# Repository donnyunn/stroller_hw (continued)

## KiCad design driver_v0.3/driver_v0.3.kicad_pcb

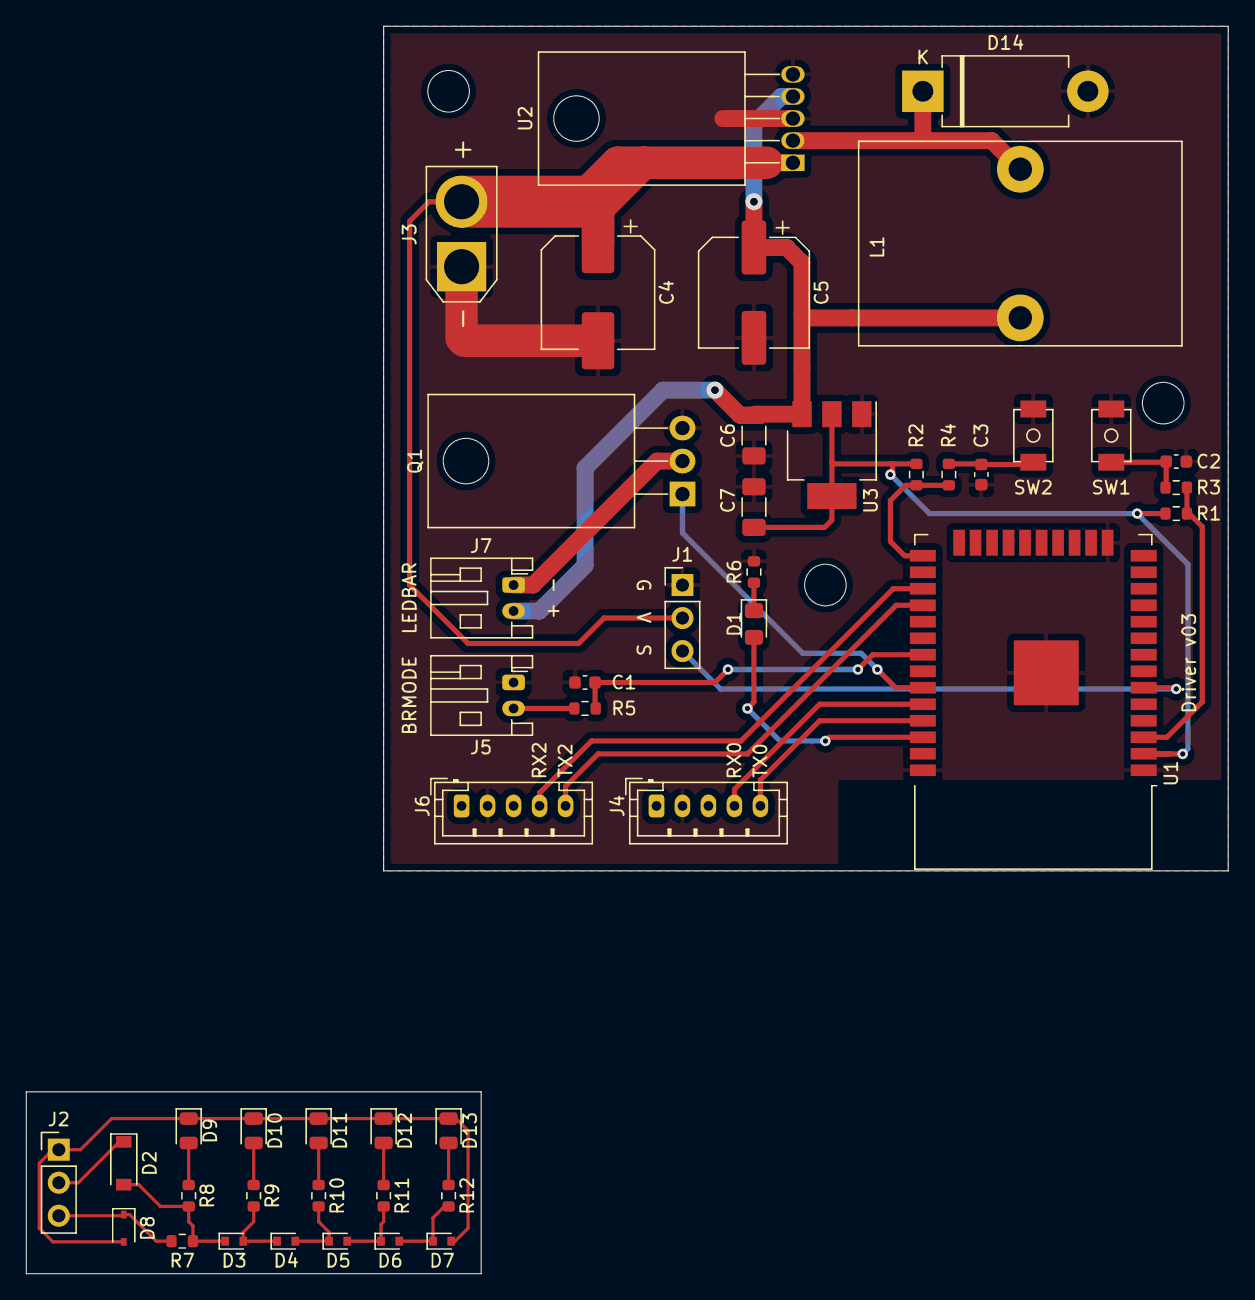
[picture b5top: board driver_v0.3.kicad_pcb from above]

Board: 2 copper layers, 92.5 x 96.0 mm, 47 parts (0 on the bottom side), 33 nets.

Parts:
C1, C2, C3: 0.1u; C_0603_1608Metric
C4: 100uF/50V; CP_Elec_8x10.5
C5: 1000uF/6.3V; CP_Elec_8x11.9
C6, C7: 4.7uF/3216; C_1206_3216Metric_Pad1.33x1.80mm_HandSolder
D1: LED; LED_0805_2012Metric_Pad1.15x1.40mm_HandSolder
D2: zenor/32v; D_SOD-123
D3, D4, D5, D6, D7: zenor/2v; D_SOD-523
D8: zenor/3.3v; D_SOD-323
D9, D10, D11, D12, D13: RED; LED_0805_2012Metric
D14: 1N5822; D_DO-201AD_P12.70mm_Horizontal
J1, J2: Conn_01x03; PinHeader_1x03_P2.54mm_Vertical
J3: Batt; AMASS_XT30U-F_1x02_P5.0mm_Vertical
J4: UART0; JST_PH_B5B-PH-K_1x05_P2.00mm_Vertical
J5: Button; JST_PH_S2B-PH-K_1x02_P2.00mm_Horizontal
J6: UART2; JST_PH_B5B-PH-K_1x05_P2.00mm_Vertical
J7: LED; JST_PH_S2B-PH-K_1x02_P2.00mm_Horizontal
L1: 100uH; L_Toroid_Vertical_L24.6mm_W15.5mm_P11.44mm_Pulse_KM-4
Q1: N-FET; TO-220-3_Horizontal_TabDown
R1, R2, R7: 100k; R_0603_1608Metric
R3, R4, R5, R12: 100; R_0603_1608Metric
R6, R8: 560; R_0603_1608Metric
R9: 430; R_0603_1608Metric
R10: 280; R_0603_1608Metric
R11: 150; R_0603_1608Metric
SW1, SW2: EN; CTT-1135P1
U1: ESP32-WROOM-32
U2: LM2576HVT-5; TO-220-5_Horizontal_TabDown
U3: LD1117S33TR_SOT223; SOT-223-3_TabPin2

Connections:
/Battery Level Guage/BATT_10CELL: D2.1, J2.2
/Battery Level Guage/BATT_GND: D7.2, D8.2, D9.1, D10.1, D11.1, D12.1, D13.1, J2.1
/Battery Level Guage/BATT_SENS: D8.1, J2.3, R7.1
BOOT: R2.2, R4.1, U1.25
EN: R1.2, R3.1, U1.3
Earth: C1.2, C2.2, C3.2, C4.2, C5.2, C6.2, C7.2, D14.2, J1.1, J3.1, J4.2, J5.1, J6.2, Q1.3, R6.2, SW1.1, SW2.1, U1.1, U1.15, U1.38, U1.39, U2.3, U2.5, U3.1
IO19(BRMODE): C1.1, R5.1, U1.31
IO21(LED): Q1.1, U1.33
IO22(IND): D1.2, U1.36
IO34(LVSENS): J1.3, U1.6
unnamed: C2.1, R3.2, SW1.2
unnamed: C3.1, R4.2, SW2.2
unnamed: D1.1, R6.1
unnamed: D2.2, D3.1, R7.2, R8.2
unnamed: D3.2, D4.1, R9.2
unnamed: D4.2, D5.1, R10.2
unnamed: D5.2, D6.1, R11.2
unnamed: D6.2, D7.1, R12.2
unnamed: D9.2, R8.1
unnamed: D10.2, R9.1
unnamed: D11.2, R10.1
unnamed: D12.2, R11.1
unnamed: D13.2, R12.1
unnamed: D14.1, L1.1, U2.2
unnamed: J5.2, R5.2
unnamed: J7.1, Q1.2
RXD0: J4.4, U1.34
RXD2: J6.4, U1.27
TXD0: J4.5, U1.35
TXD2: J6.5, U1.28
VCC: C7.1, R1.1, R2.1, U1.2, U3.2
V_BATT: C4.1, J1.2, J3.2, U2.1
V_LED: C5.1, C6.1, J7.2, L1.2, U2.4, U3.3

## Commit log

2021-07-19 2021-07-19
2021-08-13 2021-08-13
2021-09-04 2021-09-04
2021-09-06 2021-09-06
2021-11-08 2021-11-08
